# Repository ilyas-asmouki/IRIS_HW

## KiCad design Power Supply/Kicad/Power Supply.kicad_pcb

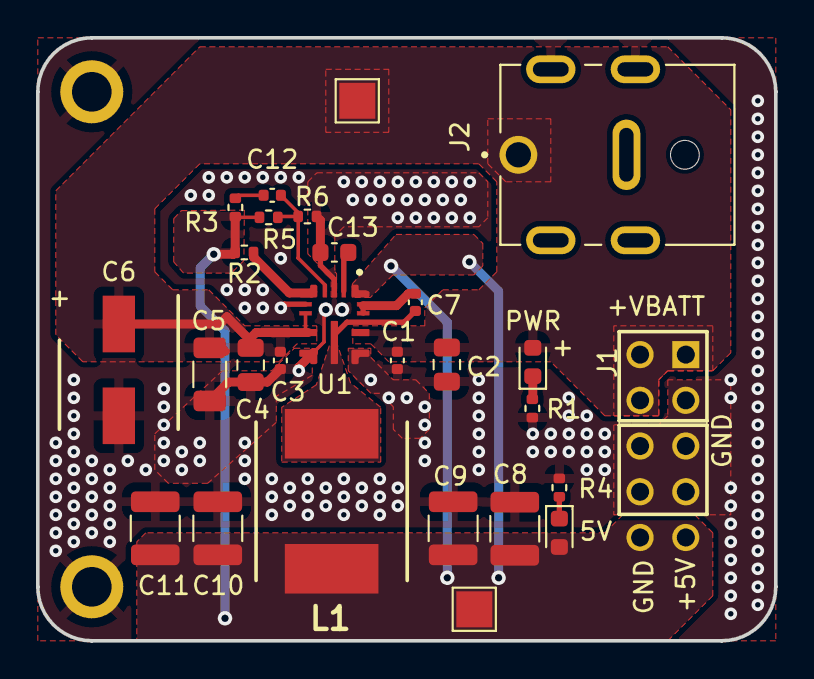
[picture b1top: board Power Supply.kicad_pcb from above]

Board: 2 copper layers, 41.0 x 33.5 mm, 29 parts (1 on the bottom side), 11 nets.

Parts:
C1, C3, C7: 100n; C_0402_1005Metric
C2, C4: 4.7u; C_0805_2012Metric
C5: 10u; C_1206_3216Metric
C6: 47u; CAPAE660X550N
C8, C9, C10, C11: 22u; C_1210_3225Metric
C12: 22p; C_0402_1005Metric
C13: 1u; C_0603_1608Metric
D1: RED; LED_0603_1608Metric
D2: GREEN; LED_0603_1608Metric
H1, H2: MountingHole_Pad; MountingHole_2.2mm_M2_ISO7380_Pad
J1: Conn_02x05_Counter_Clockwise; SULLINS_SBH11-PBPC-D05-ST-BK
J2: PJ-082BH; CUI_PJ-082BH
L1: 8.2u; INDPM8884X400N
R1, R3, R4: 1k; R_0402_1005Metric
R2: 4.7k; R_0402_1005Metric
R5: 100k; R_0402_1005Metric
R6: 24.9k; R_0402_1005Metric
TP1, TP2: TestPoint_Alt; TestPoint_Pad_2.0x2.0mm
U1: LM62440-Q1; IC_LM61460AANRJRR

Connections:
+5V: C8.1, C9.1, C10.1, C11.1, D2.2 (A), J1.9, J1.10, L1.2, R2.2, R3.1, R5.1, TP2.1, U1.1 (BIAS)
+BATT: C1.1, C2.1, C3.1, C4.1, C5.1, C6.1, D1.2 (A), J1.1, J1.2, J1.4, J2.1, TP1.1, U1.7 (EN), U1.8 (VIN1), U1.12 (VIN2)
/PS_BOOT: C7.2, U1.13 (RBOOT), U1.14 (CBOOT)
/PS_FB: C12.2, R5.2, R6.1, U1.4 (FB)
/PS_PGOOD: R2.1, U1.5 (PGOOD)
/PS_SW: C7.1, L1.1, U1.10 (SW)
/PS_VCC: C13.1, U1.2 (VCC)
GND: C1.2, C2.2, C3.2, C4.2, C5.2, C6.2, C8.2, C9.2, C10.2, C11.2, C13.2, H1.1, H2.1, J1.3, J1.5, J1.6, J1.7, J1.8, J2.2, J2.SH1 (SHIELD), J2.SH2 (SHIELD), J2.SH3 (SHIELD), J2.SH4 (SHIELD), R1.2, R4.2, R6.2, U1.3 (AGND), U1.6 (MODE/SYNC), U1.9 (PGND1), U1.11 (PGND2)
unnamed: C12.1, R3.2
unnamed: D1.1 (K), R1.1
unnamed: D2.1 (K), R4.1

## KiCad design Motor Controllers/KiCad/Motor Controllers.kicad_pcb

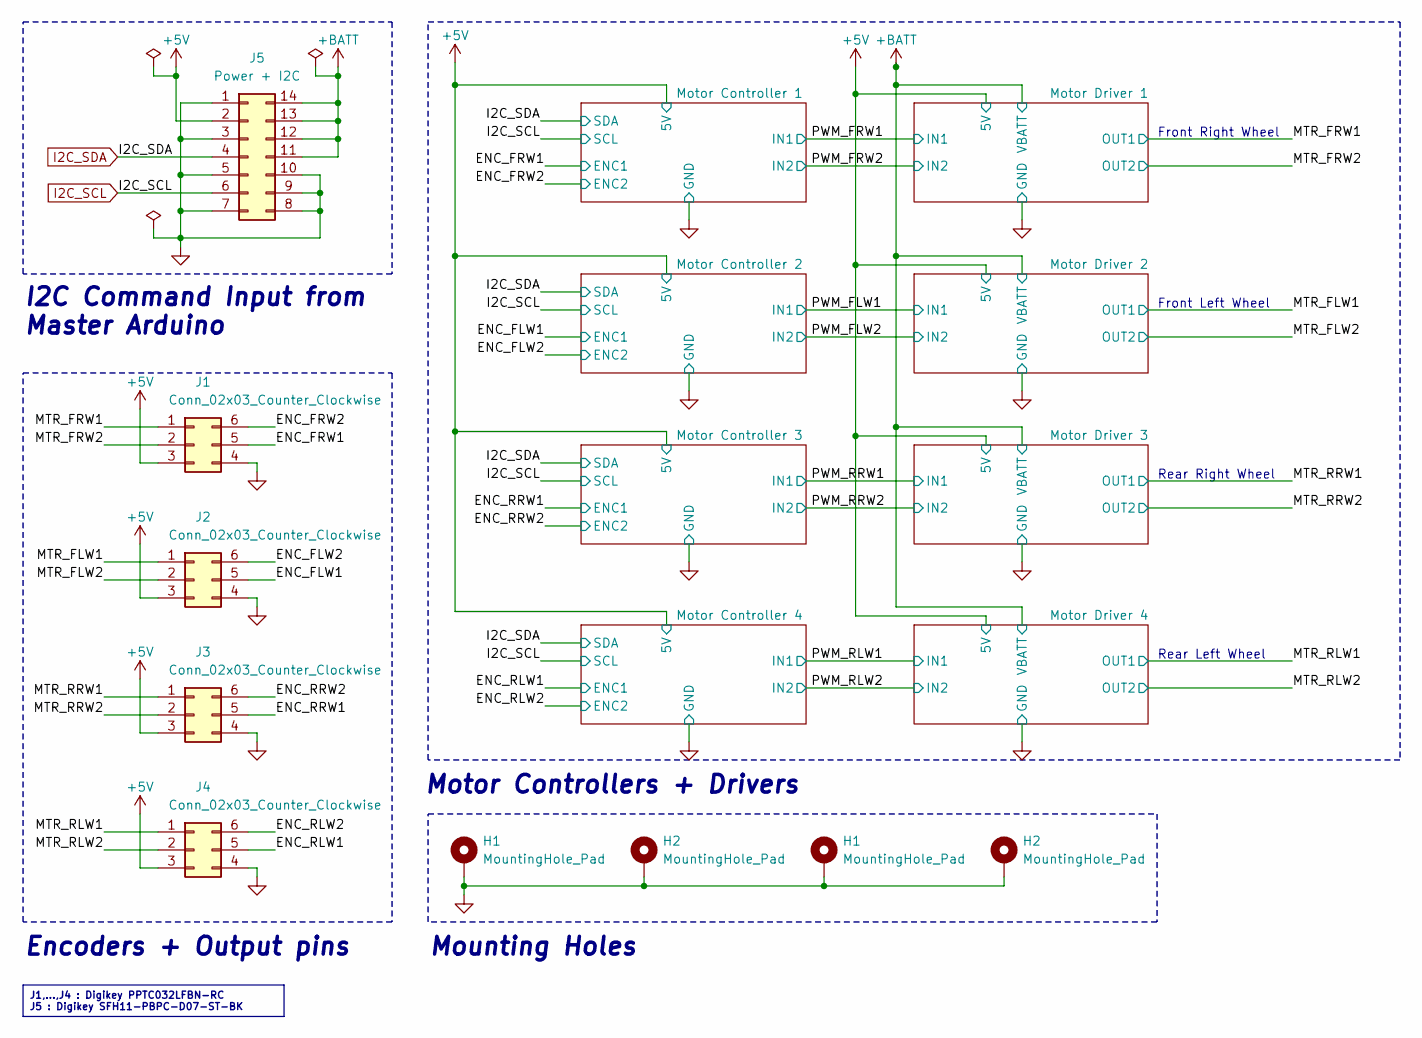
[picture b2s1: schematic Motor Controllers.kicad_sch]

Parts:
H1, H2: MountingHole_Pad; MountingHole_2.2mm_M2_ISO7380_Pad
J1, J2, J3, J4: Conn_02x03_Counter_Clockwise; SULLINS_PPTC032LFBN-RC
J5: Power + I2C; SULLINS_SFH11-PBPC-D07-ST-BK

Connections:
+5V: J1.3, J2.3, J3.3, J4.3, J5.2; also elsewhere on the board
+BATT: J5.11, J5.12, J5.13, J5.14; also elsewhere on the board
/ENC_FLW1: J2.5; also elsewhere on the board
/ENC_FLW2: J2.6; also elsewhere on the board
/ENC_FRW1: J1.5; also elsewhere on the board
/ENC_FRW2: J1.6; also elsewhere on the board
/ENC_RLW1: J4.5; also elsewhere on the board
/ENC_RLW2: J4.6; also elsewhere on the board
/ENC_RRW1: J3.5; also elsewhere on the board
/ENC_RRW2: J3.6; also elsewhere on the board
/MTR_FLW1: J2.1; also elsewhere on the board
/MTR_FLW2: J2.2; also elsewhere on the board
/MTR_FRW1: J1.1; also elsewhere on the board
/MTR_FRW2: J1.2; also elsewhere on the board
/MTR_RLW1: J4.1; also elsewhere on the board
/MTR_RLW2: J4.2; also elsewhere on the board
/MTR_RRW1: J3.1; also elsewhere on the board
/MTR_RRW2: J3.2; also elsewhere on the board
GND: H1.1, H2.1, J1.4, J2.4, J3.4, J4.4, J5.1, J5.3, J5.5, J5.7, J5.8, J5.9, J5.10; also elsewhere on the board
I2C_SCL: J5.6; also elsewhere on the board
I2C_SDA: J5.4; also elsewhere on the board

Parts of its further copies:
H3, H4: MountingHole_Pad; MountingHole_2.2mm_M2_ISO7380_Pad

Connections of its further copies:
GND: H3.1, H4.1; also elsewhere on the board

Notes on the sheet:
J1,...,J4 : Digikey PPTC032LFBN-RC J5 : Digikey SFH11-PBPC-D07-ST-BK
Mounting Holes
Rear Right Wheel
Rear Left Wheel
I2C Command Input from Master Arduino
Motor Controllers + Drivers
Front Left Wheel
Encoders + Output pins
Front Right Wheel

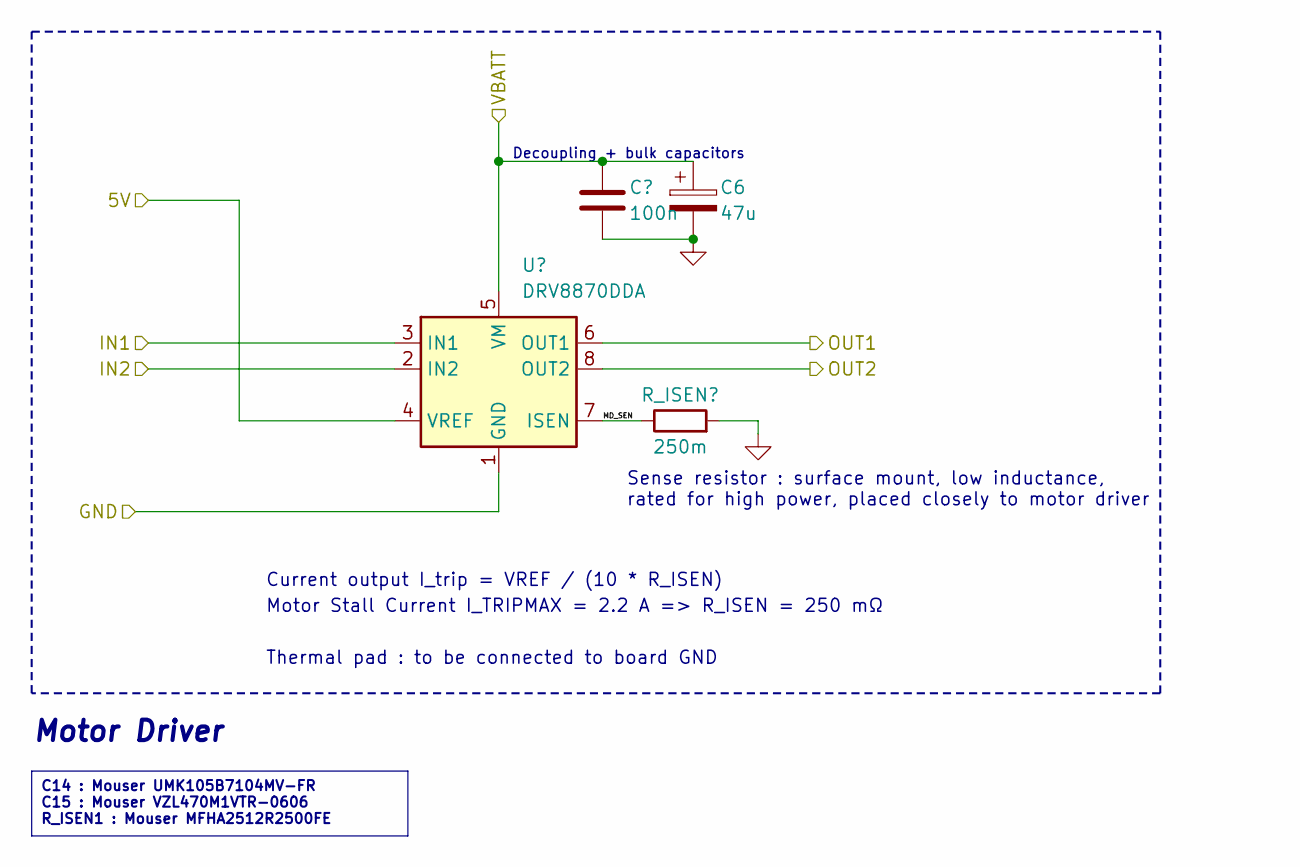
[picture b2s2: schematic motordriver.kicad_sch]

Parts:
C6: 47u; CAPAE660X550N
C14: 100n; C_0402_1005Metric
R_ISEN1: 250m; R_2512_6332Metric
U2: DRV8870DDA; Texas_HTSOP-8-1EP_3.9x4.9mm_P1.27mm_EP2.95x4.9mm_Mask2.4x3.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

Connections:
+5V: U2.4 (VREF); also elsewhere on the board
+BATT: C14.1, U2.5 (VM); also elsewhere on the board
/MTR_FLW1: U2.6 (OUT1); also elsewhere on the board
/MTR_FLW2: U2.8 (OUT2); also elsewhere on the board
/PWM_FLW1: U2.3 (IN1); also elsewhere on the board
/PWM_FLW2: U2.2 (IN2); also elsewhere on the board
GND: C14.2, R_ISEN1.2, U2.1 (GND), U2.9 (GND); also elsewhere on the board

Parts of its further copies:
C15, C17, C19, C21: 47u; CAPAE660X550N
C16, C18, C20: 100n; C_0402_1005Metric
R_ISEN2, R_ISEN3, R_ISEN4: 250m; R_2512_6332Metric
U1, U3, U4: DRV8870DDA; Texas_HTSOP-8-1EP_3.9x4.9mm_P1.27mm_EP2.95x4.9mm_Mask2.4x3.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

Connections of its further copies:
+5V: U1.4 (VREF), U3.4 (VREF), U4.4 (VREF); also elsewhere on the board
+BATT: C15.1, C16.1, C17.1, C18.1, C19.1, C20.1, C21.1, U1.5 (VM), U3.5 (VM), U4.5 (VM); also elsewhere on the board
/MTR_FRW1: U1.6 (OUT1); also elsewhere on the board
/MTR_FRW2: U1.8 (OUT2); also elsewhere on the board
/MTR_RLW1: U4.6 (OUT1); also elsewhere on the board
/MTR_RLW2: U4.8 (OUT2); also elsewhere on the board
/MTR_RRW1: U3.6 (OUT1); also elsewhere on the board
/MTR_RRW2: U3.8 (OUT2); also elsewhere on the board
/Motor Driver 3/MD_SEN: R_ISEN3.1, U3.7 (ISEN)
/Motor Driver 4/MD_SEN: R_ISEN4.1, U4.7 (ISEN)
/PWM_FRW1: U1.3 (IN1); also elsewhere on the board
/PWM_FRW2: U1.2 (IN2); also elsewhere on the board
/PWM_RLW1: U4.3 (IN1); also elsewhere on the board
/PWM_RLW2: U4.2 (IN2); also elsewhere on the board
/PWM_RRW1: U3.3 (IN1); also elsewhere on the board
/PWM_RRW2: U3.2 (IN2); also elsewhere on the board
GND: C15.2, C16.2, C17.2, C18.2, C19.2, C20.2, C21.2, R_ISEN2.2, R_ISEN3.2, R_ISEN4.2, U1.1 (GND), U1.9 (GND), U3.1 (GND), U3.9 (GND), U4.1 (GND), U4.9 (GND); also elsewhere on the board

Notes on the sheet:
Sense resistor : surface mount, low inductance, rated for high power, placed closely to motor driver
C14 : Mouser UMK105B7104MV-FR C15 : Mouser VZL470M1VTR-0606 R_ISEN1 : Mouser MFHA2512R2500FE
Decoupling + bulk capacitors
Current output I_trip = VREF / (10 * R_ISEN)
Motor Stall Current I_TRIPMAX = 2.2 A => R_ISEN = 250 mΩ
Motor Driver
Thermal pad : to be connected to board GND

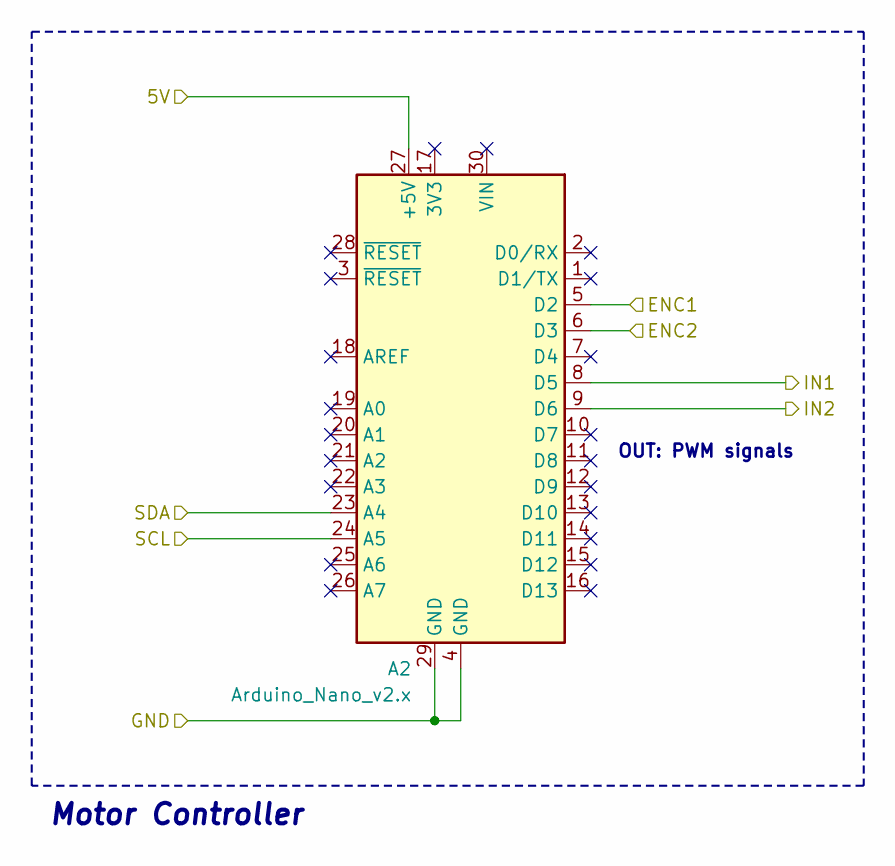
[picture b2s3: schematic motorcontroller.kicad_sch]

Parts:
A2: Arduino_Nano_v2.x; Arduino_Nano

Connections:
+5V: A2.27 (+5V); also elsewhere on the board
/ENC_FLW1: A2.5 (D2); also elsewhere on the board
/ENC_FLW2: A2.6 (D3); also elsewhere on the board
/PWM_FLW1: A2.8 (D5); also elsewhere on the board
/PWM_FLW2: A2.9 (D6); also elsewhere on the board
GND: A2.4 (GND), A2.29 (GND); also elsewhere on the board
I2C_SCL: A2.24 (A5); also elsewhere on the board
I2C_SDA: A2.23 (A4); also elsewhere on the board

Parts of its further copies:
A1, A3, A4: Arduino_Nano_v2.x; Arduino_Nano

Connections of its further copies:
+5V: A1.27 (+5V), A3.27 (+5V), A4.27 (+5V); also elsewhere on the board
/ENC_FRW1: A1.5 (D2); also elsewhere on the board
/ENC_FRW2: A1.6 (D3); also elsewhere on the board
/ENC_RLW1: A4.5 (D2); also elsewhere on the board
/ENC_RLW2: A4.6 (D3); also elsewhere on the board
/ENC_RRW1: A3.5 (D2); also elsewhere on the board
/ENC_RRW2: A3.6 (D3); also elsewhere on the board
/PWM_FRW1: A1.8 (D5); also elsewhere on the board
/PWM_FRW2: A1.9 (D6); also elsewhere on the board
/PWM_RLW1: A4.8 (D5); also elsewhere on the board
/PWM_RLW2: A4.9 (D6); also elsewhere on the board
/PWM_RRW1: A3.8 (D5); also elsewhere on the board
/PWM_RRW2: A3.9 (D6); also elsewhere on the board
GND: A1.4 (GND), A1.29 (GND), A3.4 (GND), A3.29 (GND), A4.4 (GND), A4.29 (GND); also elsewhere on the board
I2C_SCL: A1.24 (A5), A3.24 (A5), A4.24 (A5); also elsewhere on the board
I2C_SDA: A1.23 (A4), A3.23 (A4), A4.23 (A4); also elsewhere on the board

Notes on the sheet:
Motor Controller
OUT: PWM signals

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
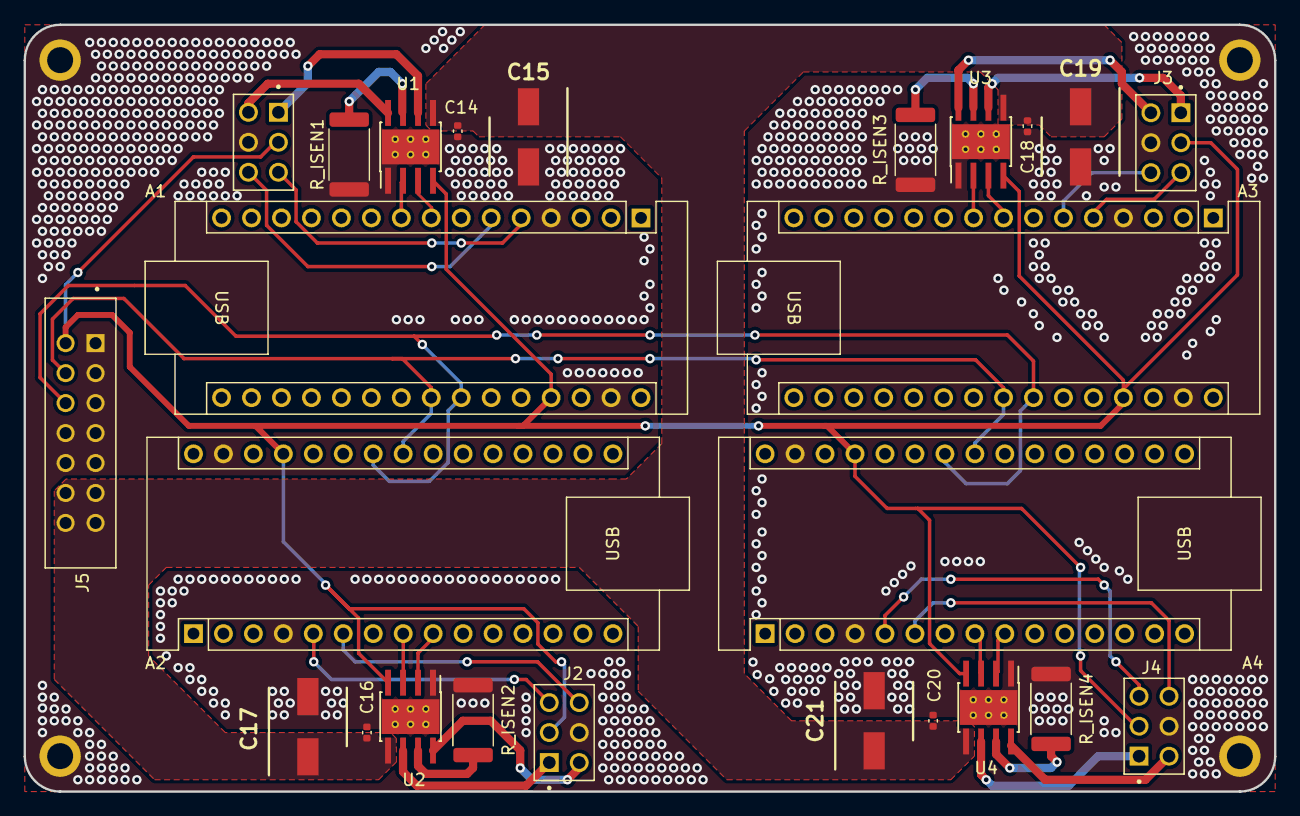
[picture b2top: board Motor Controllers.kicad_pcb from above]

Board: 2 copper layers, 106.0 x 65.0 mm, 29 parts (0 on the bottom side), 33 nets.

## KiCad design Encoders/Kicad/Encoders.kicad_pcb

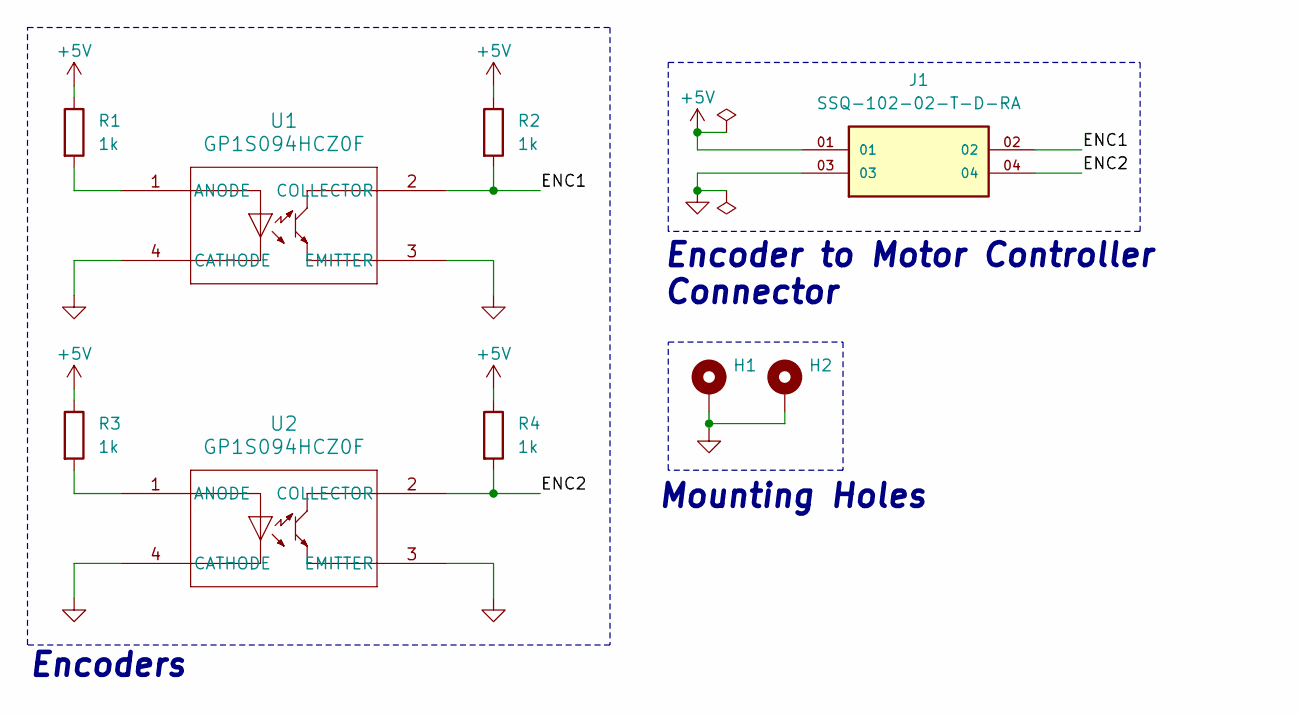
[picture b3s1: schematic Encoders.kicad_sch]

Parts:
H1, H2: MountingHole_Pad; MountingHole_2.2mm_M2_ISO7380_Pad_TopBottom
J1: SSQ-102-02-T-D-RA; SAMTEC_SSQ-102-02-T-D-RA; PARTREV R
R1, R2, R3, R4: 1k; R_0402_1005Metric
U1, U2: GP1S094HCZ0F

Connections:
+5V: J1.01, R1.1, R2.1, R3.1, R4.1
/ENC1: J1.02, R2.2, U1.2 (COLLECTOR)
/ENC2: J1.04, R4.2, U2.2 (COLLECTOR)
GND: H1.1, H2.1, J1.03, U1.3 (EMITTER), U1.4 (CATHODE), U2.3 (EMITTER), U2.4 (CATHODE)
unnamed: R1.2, U1.1 (ANODE)
unnamed: R3.2, U2.1 (ANODE)

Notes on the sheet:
Encoders
Encoder to Motor Controller Connector
Mounting Holes

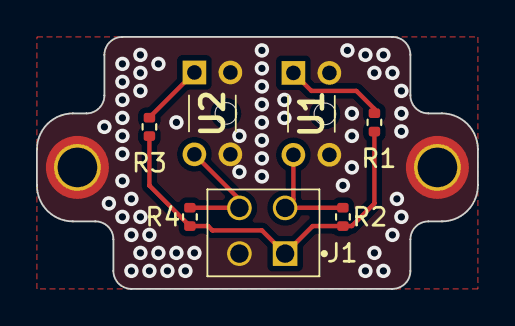
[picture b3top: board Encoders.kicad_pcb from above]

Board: 2 copper layers, 24.5 x 14.0 mm, 9 parts (0 on the bottom side), 6 nets.

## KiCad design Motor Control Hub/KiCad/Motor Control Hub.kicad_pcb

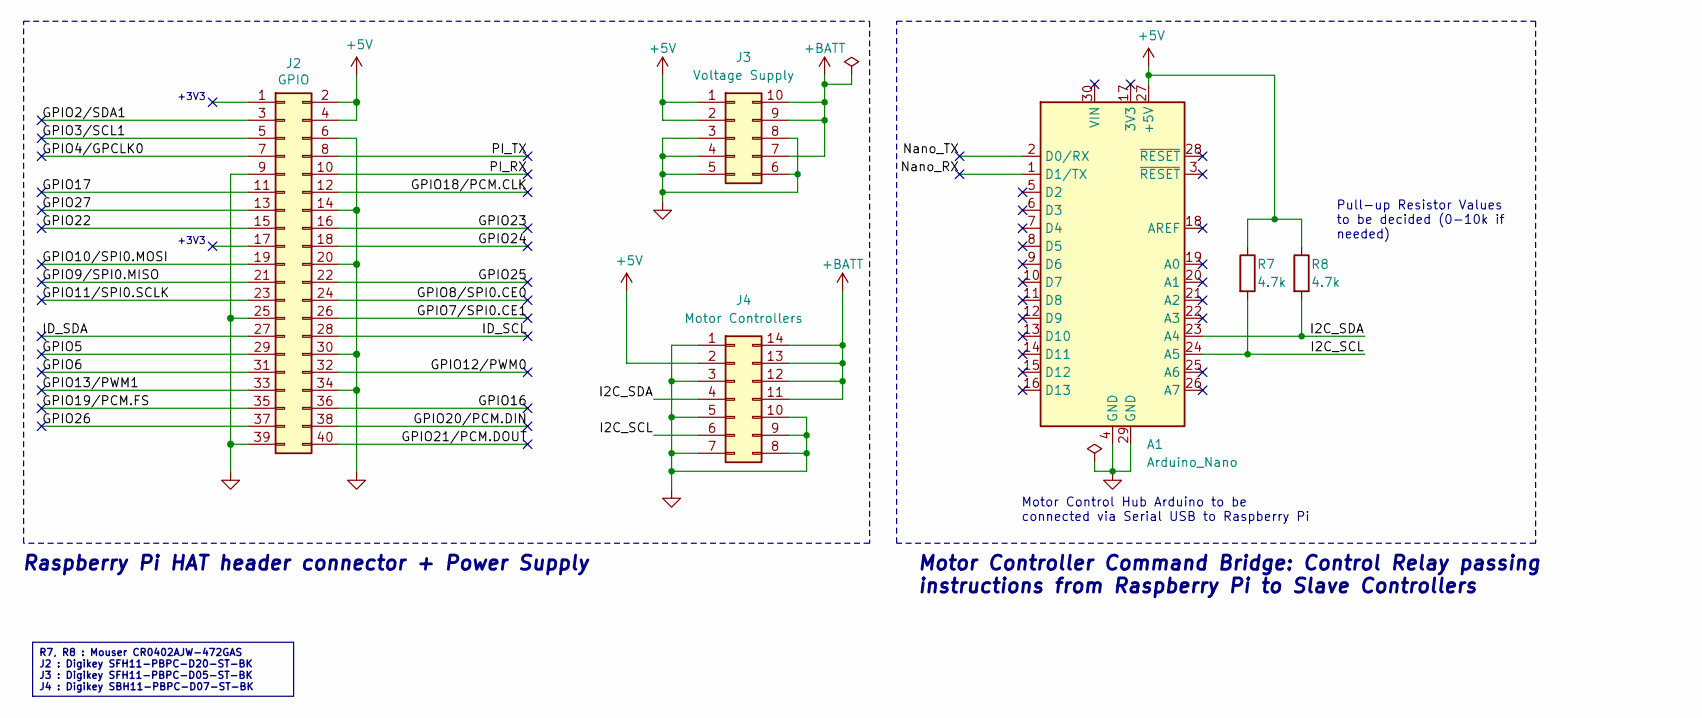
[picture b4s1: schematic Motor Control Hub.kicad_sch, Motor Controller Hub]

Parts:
A1: Arduino_Nano
J2: GPIO; CONN_SFH11-PBPC-D20-ST-BK_SUL
J3: Voltage Supply; CONN_SFH11-xxxC-D05-ST-XX_SUL
J4: Motor Controllers; SHDR14W64P254_2X7_2528X910X910P
R7, R8: 4.7k; R_0402_1005Metric

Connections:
+5V: A1.27 (+5V), J2.2, J2.4, J3.1, J3.2, J4.2, R7.1, R8.1
+BATT: J3.7, J3.9, J3.10, J4.11, J4.12, J4.13, J4.14
/GPIO2/SDA1: J2.3
/GPIO3/SCL1: J2.5
/GPIO4/GPCLK0: J2.7
/GPIO5: J2.29
/GPIO6: J2.31
/GPIO7/SPI0.CE1: J2.26
/GPIO8/SPI0.CE0: J2.24
/GPIO9/SPI0.MISO: J2.21
/GPIO10/SPI0.MOSI: J2.19
/GPIO11/SPI0.SCLK: J2.23
/GPIO12/PWM0: J2.32
/GPIO13/PWM1: J2.33
/GPIO16: J2.36
/GPIO17: J2.11
/GPIO18/PCM.CLK: J2.12
/GPIO19/PCM.FS: J2.35
/GPIO20/PCM.DIN: J2.38
/GPIO21/PCM.DOUT: J2.40
/GPIO22: J2.15
/GPIO23: J2.16
/GPIO24: J2.18
/GPIO25: J2.22
/GPIO26: J2.37
/GPIO27: J2.13
/I2C_SCL: A1.24 (A5), J4.6, R7.2
/I2C_SDA: A1.23 (A4), J4.4, R8.2
/ID_SCL: J2.28
/ID_SDA: J2.27
/Nano_RX: A1.1 (D1/TX)
/Nano_TX: A1.2 (D0/RX)
/PI_RX: J2.10
/PI_TX: J2.8
GND: A1.4 (GND), A1.29 (GND), J2.6, J2.9, J2.14, J2.20, J2.25, J2.30, J2.34, J2.39, J3.3, J3.4, J3.5, J3.6, J3.8, J4.1, J4.3, J4.5, J4.7, J4.8, J4.9, J4.10

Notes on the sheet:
Motor Control Hub Arduino to be connected via Serial USB to Raspberry Pi
R7, R8 : Mouser CR0402AJW-472GAS J2 : Digikey SFH11-PBPC-D20-ST-BK J3 : Digikey SFH11-PBPC-D05-ST-BK J4 : Digikey SBH11-PBPC-D07-ST-BK
Pull-up Resistor Values to be decided (0-10k if needed)
Motor Controller Command Bridge: Control Relay passing instructions from Raspberry Pi to Slave Controllers
Raspberry Pi HAT header connector + Power Supply
+3V3

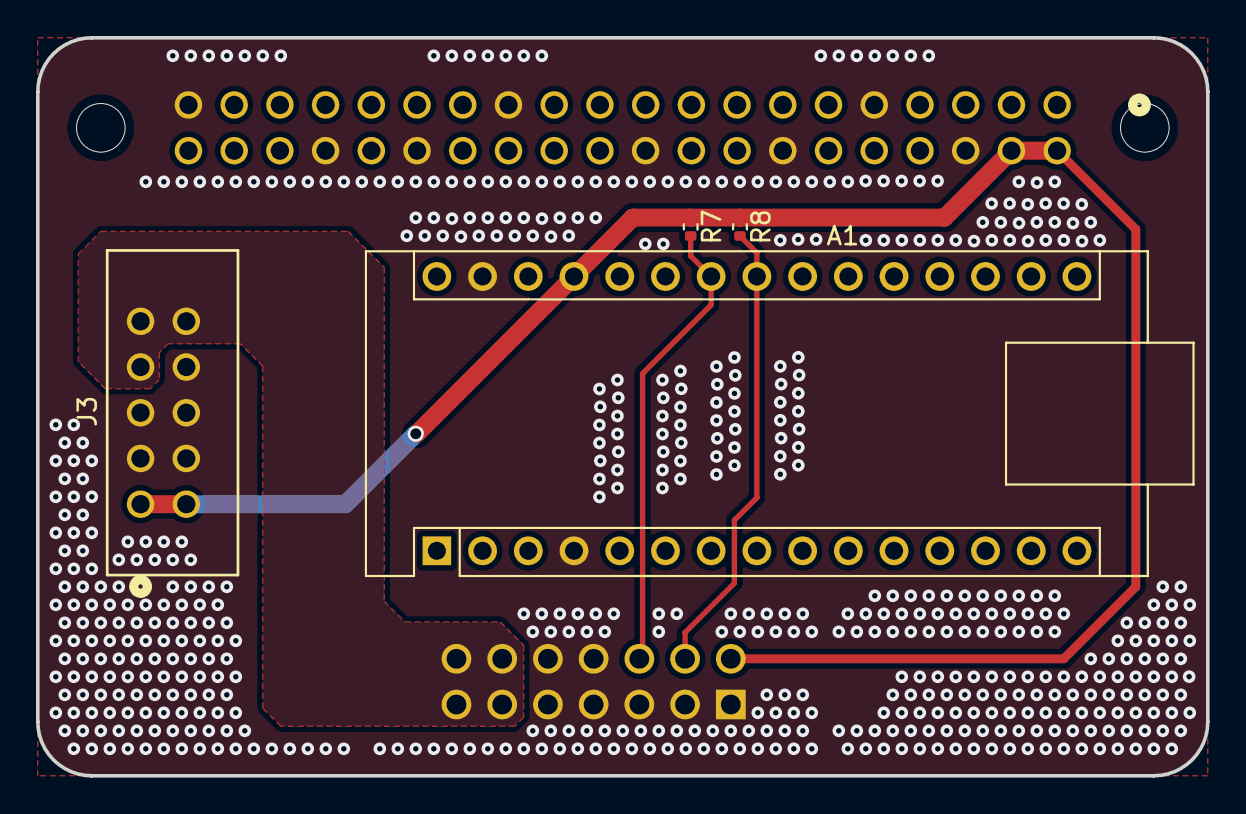
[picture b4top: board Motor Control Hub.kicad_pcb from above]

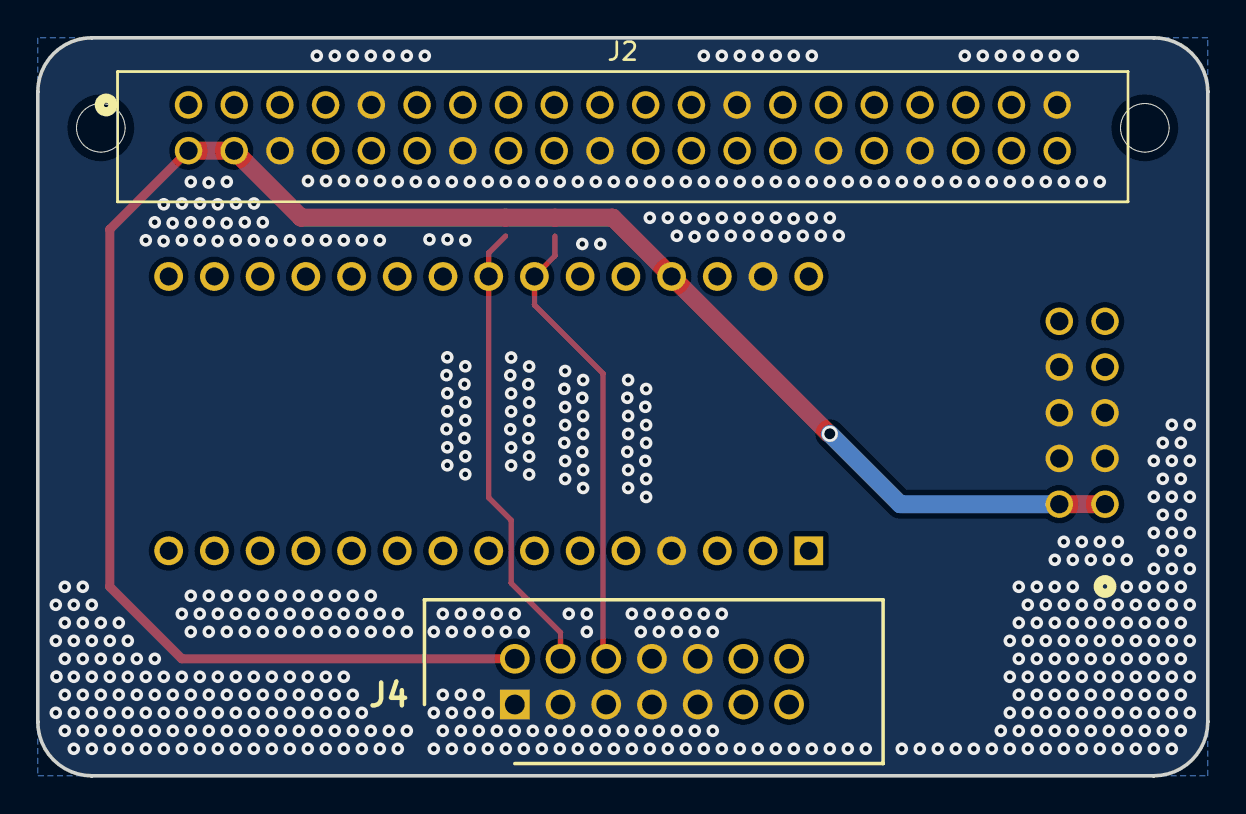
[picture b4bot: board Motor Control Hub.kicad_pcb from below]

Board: 2 copper layers, 65.0 x 41.0 mm, 8 parts (2 on the bottom side), 5 nets.

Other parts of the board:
MH1, MH2: MountingHole_2.7mm_M2.5

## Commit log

2024-04-20 First Commit of Motor Control Hub
2024-04-20 First Commit of Motor Controllers
2024-05-07 added encoders, slightly adjusted copper tracks
2024-10-25 added Arduino FW for completeness
